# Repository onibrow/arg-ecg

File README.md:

# Arias Research Group - BLE ECG

## References

### BLE

Task - Use the nRF52 Development Kit to send ECG data from the ADAS1000 over BLE to a phone to record data.

After careful assesment, I've decided to move forward with the Arduino BLEPeripheral library, after finding that someone has ported the SoftDevice functionality to Arduino IDE. This was mainly due to my unfamiliarity with the BLE stack, and the daunting, semeingly unknown and unfriendly Nordic toolchain.

To get it to work, I had to install a few packages:

```
libstdc++5
lib32-libstdc++5
libudev0-shim
gperf
lib32-attr
lib32-libcap
lib32-libgpg-error
libg32-libgcrypt
lib32-system
lib32-libudev0-shim
```

[nRF5 board files](https://github.com/sandeepmistry/arduino-nRF5)

[Arduino BLEPeripheral](https://github.com/sandeepmistry/arduino-BLEPeripheral)



### ADAS1000

[ADAS1000 Datasheet](https://www.analog.com/media/en/technical-documentation/data-sheets/ADAS1000_1000-1_1000-2.pdf)

[Eval Board Datasheet](http://www.analog.com/media/en/technical-documentation/user-guides/UG-426.pdf)

[Reference Design](https://www.analog.com/media/en/reference-design-documentation/reference-designs/CN0308.pdf)

There are two ADAS's on the eval board, one master one slave for a total of 12 electrode input. We'll utilize only 5 of them from the master chip using the pins LA, RA, LL, RLD, V1, V2. RLD (Right Leg Driver) can also be used as the common mode electrode. We can choose different electrode setups after we get the hardware to work by toggling what we want to use and get the optimal setup

SPI communication details

* Clock Polarity: Idle HIGH
* Clock Phase: Data is clocked into ADAS during the rising edges of SCLK, and shifted out (to be read) on falling edges of SCLK

[SPI Register Defs Page 60](https://www.analog.com/media/en/technical-documentation/data-sheets/ADAS1000_1000-1_1000-2.pdf)

### CC3200MOD\[DEPRACATED\] (WiFi)

[CC3200MOD Datasheet](http://www.ti.com/lit/ds/swrs166/swrs166.pdf)

[CC3200MOD LaunchPad User Guide](http://www.ti.com/lit/ug/swru397a/swru397a.pdf)

[CC3200MOD LaunchPad Schematic](http://www.ti.com/lit/df/tidrc48/tidrc48.pdf)

[CC3200 Jumper Settings](http://energia.nu/guide/install/cc3200-guide/)

[CC3200 SPI <-> ADAS1000](https://ez.analog.com/linux-device-drivers/microcontroller-no-os-drivers/f/q-a/88100/adas-1000-to-arduino-code)

[More SPI stuff](https://www.element14.com/community/thread/46120/l/adas1000-interfacing-by-arduino-uno?displayFullThread=true)

## Other Wifi Modules

[ThingSpeak](https://thingspeak.com/)

[ESP8266](https://www.sparkfun.com/products/13678)

## IoT Server

Thinger.io is pretty nice - also has good integration with the launchpad - [Link](http://docs.thinger.io/arduino/#installation)

## Parts

All SMD components will be 0602 unless specified.

[8.192MHz](https://www.digikey.com/product-detail/en/citizen-finedevice-co-ltd/CM309S8.192MABJT/300-2039-1-ND/482155)

[1uH Inductor](https://www.digikey.com/product-detail/en/tdk-corporation/MLZ2012M1R0HT000/445-8657-1-ND/3077939)

[Chip Antenna](https://www.digikey.com/product-detail/en/taiyo-yuden/AH316M245001-T/587-2200-1-ND/2002898)

[DP3T](https://www.digikey.com/product-detail/en/c-k/JS203011JCQN/CKN10725CT-ND/6137639)

[2Pin JST](https://www.digikey.com/product-detail/en/jst-sales-america-inc/B2B-XH-A(LF)(SN)/455-2247-ND/1651045)

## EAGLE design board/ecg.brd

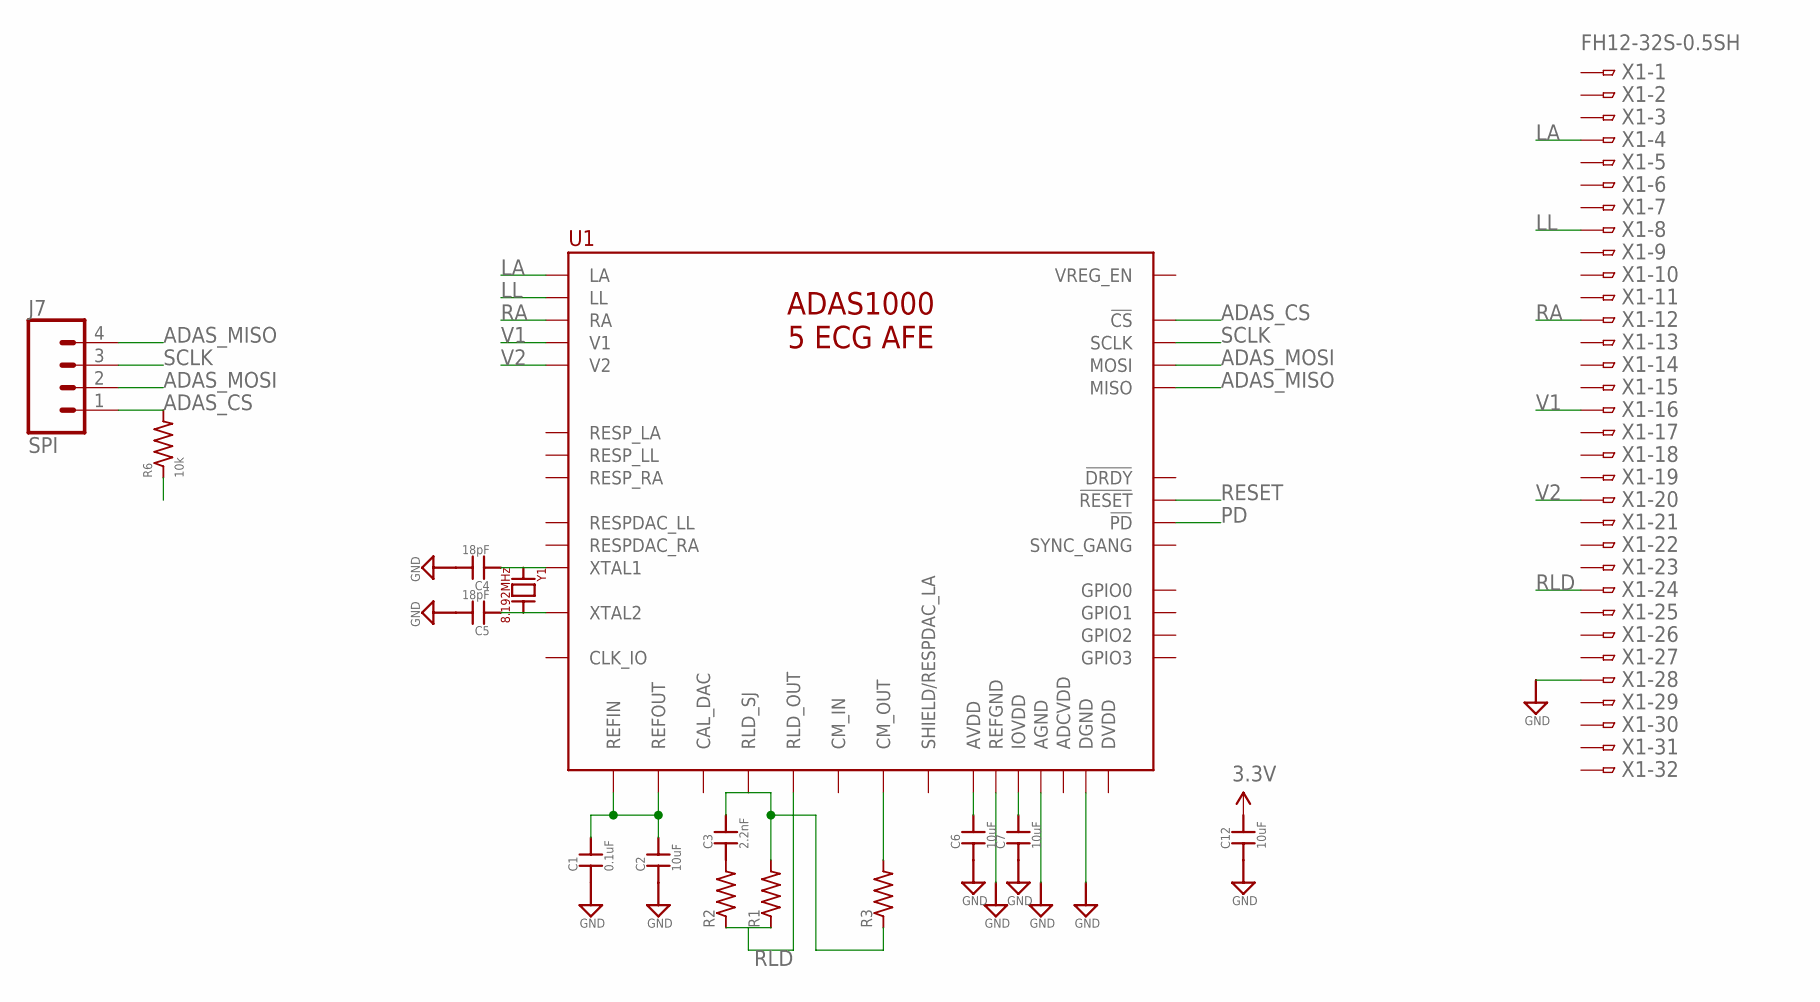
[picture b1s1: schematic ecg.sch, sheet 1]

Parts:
C1: 0.1uF; 0603-CAP
C2, C6, C7, C12: 10uF; 0603-CAP
C3: 2.2nF; 0603-CAP
C4, C5: 18pF; 0603-CAP
J7: SPI; 1X04
R1: 4M; R0603
R2: 100k; R0603
R3: 40k; R0603
R6: 10k; R0603
U1: ADAS1000; QFP50P1200X1200X160-65N
X1: FH12-32S-0.5SH
Y1: 8.192MHz; HC-49

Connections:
3.3V: C6.2, C7.2, C12.2, R6.1, U1.18 (AVDD), U1.23 (AVDD), U1.35 (IOVDD), U1.46 (IOVDD), U1.58 (AVDD), U1.63 (AVDD); also elsewhere on the board
ADAS_CS: J7.1, R6.2, U1.41 (!CS); also elsewhere on the board
ADAS_MISO: J7.4, U1.45 (MISO); also elsewhere on the board
ADAS_MOSI: J7.2, U1.43 (MOSI); also elsewhere on the board
GND: C1.1, C2.1, C4.2, C5.2, C6.1, C7.1, C12.1, U1.2 (AGND), U1.7 (REFGND), U1.15 (AGND), U1.24 (AGND), U1.25 (AGND), U1.31 (DGND), U1.34 (DGND), U1.40 (DGND), U1.47 (DGND), U1.50 (DGND), U1.56 (AGND), U1.57 (AGND), X1.28; also elsewhere on the board
LA: U1.10 (LA), X1.4
LL: U1.11 (LL), X1.8
unnamed: C1.2, C2.2, U1.8 (REFOUT), U1.9 (REFIN)
unnamed: C3.2, R1.2, R3.1, U1.21 (RLD_SJ)
unnamed: C3.1, R2.2
unnamed: R3.2, U1.22 (CM_OUT)
unnamed: C4.1, U1.27 (XTAL1), Y1.A
unnamed: C5.1, U1.28 (XTAL2), Y1.B
PD: U1.53 (!PD)
RA: U1.12 (RA), X1.12
RESET: U1.54 (!RESET)
RLD: R1.1, R2.1, U1.20 (RLD_OUT), X1.24
SCLK: J7.3, U1.44 (SCLK); also elsewhere on the board
V1: U1.13 (V1), X1.16
V2: U1.14 (V2), X1.20

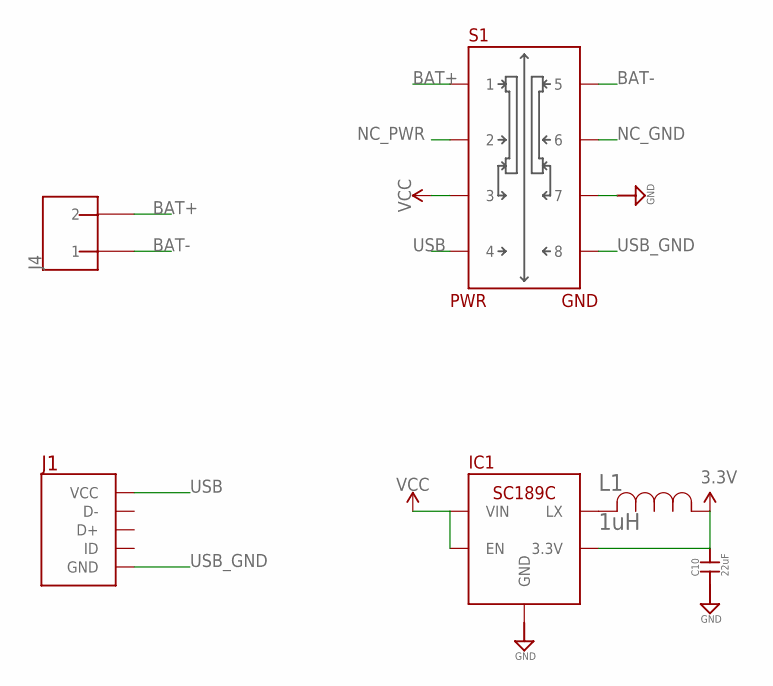
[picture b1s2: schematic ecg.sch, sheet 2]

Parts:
C10: 22uF; 0603-CAP
IC1: SC189C; SOT23-5
J1: USB_MICRO
J4: 2_PIN_JST-XH
L1: 1uH; IND_2012
S1: DP3T

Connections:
3.3V: C10.2, IC1.4 (3.3V), L1.1; also elsewhere on the board
BAT+: J4.P$2 (2), S1.1
BAT-: J4.P$1 (1), S1.5
GND: C10.1, IC1.2 (GND), S1.7; also elsewhere on the board
unnamed: IC1.5 (LX), L1.2
NC_GND: S1.6
NC_PWR: S1.2
USB: J1.VCC, S1.4
USB_GND: J1.GND, S1.8
VCC: IC1.1 (VIN), IC1.3 (EN), S1.3

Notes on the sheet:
PWR
GND

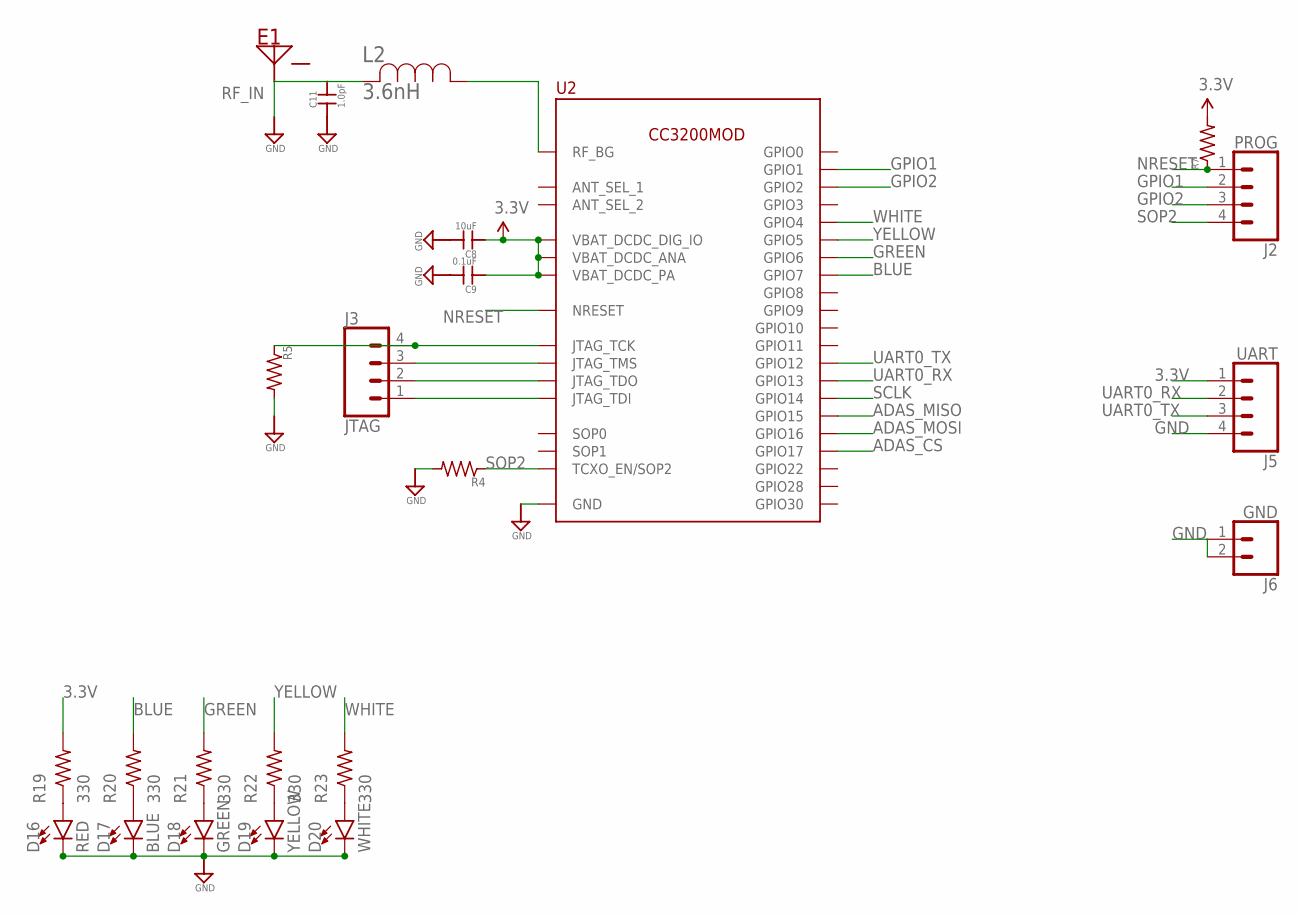
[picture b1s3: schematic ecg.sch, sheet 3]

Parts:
C8: 10uF; 0603-CAP
C9: 0.1uF; 0603-CAP
C11: 1.0pF; 0603-CAP
D16: RED; LED-0603
D17: BLUE; LED-0603
D18: GREEN; LED-0603
D19: YELLOW; LED-0603
D20: WHITE; LED-0603
E1: AH316M245001-T; CHIP_ANT
J2: PROG; 1X04
J3: JTAG; 1X04
J5: UART; 1X04
J6: GND; 1X02
L2: 3.6nH; IND0402_22N_TAI
R4: 2.7k; R0603
R5: 100k; R0603
R7: R-US_R0603; R0603
R19, R20, R21, R22, R23: 330; R0402
U2: CC3200MOD; 63-SMD

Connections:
3.3V: C8.1, C9.1, J5.1, R7.2, R19.2, U2.P$36 (VBAT_DCDC_ANA), U2.P$37 (VBAT_DCDC_PA), U2.P$40 (VBAT_DCDC_DIG_IO); also elsewhere on the board
ADAS_CS: U2.P$8 (GPIO17); also elsewhere on the board
ADAS_MISO: U2.P$6 (GPIO15); also elsewhere on the board
ADAS_MOSI: U2.P$7 (GPIO16); also elsewhere on the board
BLUE: R20.2, U2.P$52 (GPIO7)
GND: C8.2, C9.2, C11.1, D16.C, D17.C, D18.C, D19.C, D20.C, J5.4, J6.1, J6.2, R4.2, R5.2, U2.P$1 (GND), U2.P$2 (GND), U2.P$16 (GND), U2.P$27 (GND), U2.P$28 (GND), U2.P$30 (GND), U2.P$32 (GND), U2.P$38 (GND), U2.P$43 (GND), U2.P$55 (GND), U2.P$56 (GND), U2.P$57 (GND), U2.P$58 (GND), U2.P$59 (GND), U2.P$60 (GND), U2.P$61 (GND), U2.P$62 (GND), U2.P$63 (GND); also elsewhere on the board
GPIO1: J2.2, U2.P$46 (GPIO1)
GPIO2: J2.3, U2.P$47 (GPIO2)
GREEN: R21.2, U2.P$51 (GPIO6)
unnamed: J3.4, R5.1, U2.P$21 (JTAG_TCK)
unnamed: J3.3, U2.P$22 (JTAG_TMS)
unnamed: J3.2, U2.P$18 (JTAG_TDO)
unnamed: J3.1, U2.P$12 (JTAG_TDI)
unnamed: D16.A, R19.1
unnamed: D17.A, R20.1
unnamed: D18.A, R21.1
unnamed: D19.A, R22.1
unnamed: D20.A, R23.1
NRESET: J2.1, R7.1, U2.P$35 (NRESET)
RF_BG: L2.1, U2.P$31 (RF_BG)
RF_IN: C11.2, E1.INPUT, L2.2
SCLK: U2.P$5 (GPIO14); also elsewhere on the board
SOP2: J2.4, R4.1, U2.P$23 (TCXO_EN/SOP2)
UART0_RX: J5.2, U2.P$10 (GPIO13)
UART0_TX: J5.3, U2.P$9 (GPIO12)
WHITE: R23.2, U2.P$49 (GPIO4)
YELLOW: R22.2, U2.P$50 (GPIO5)

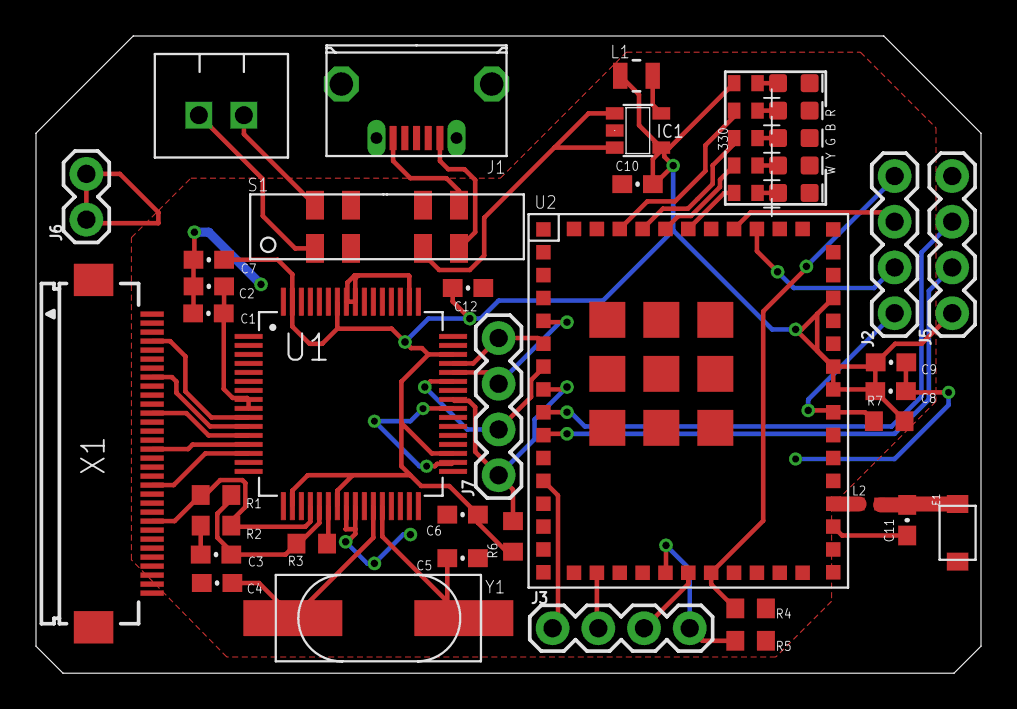
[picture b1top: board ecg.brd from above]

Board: 2 copper layers, 52.5 x 35.4 mm, 45 parts (0 on the bottom side), 45 nets.

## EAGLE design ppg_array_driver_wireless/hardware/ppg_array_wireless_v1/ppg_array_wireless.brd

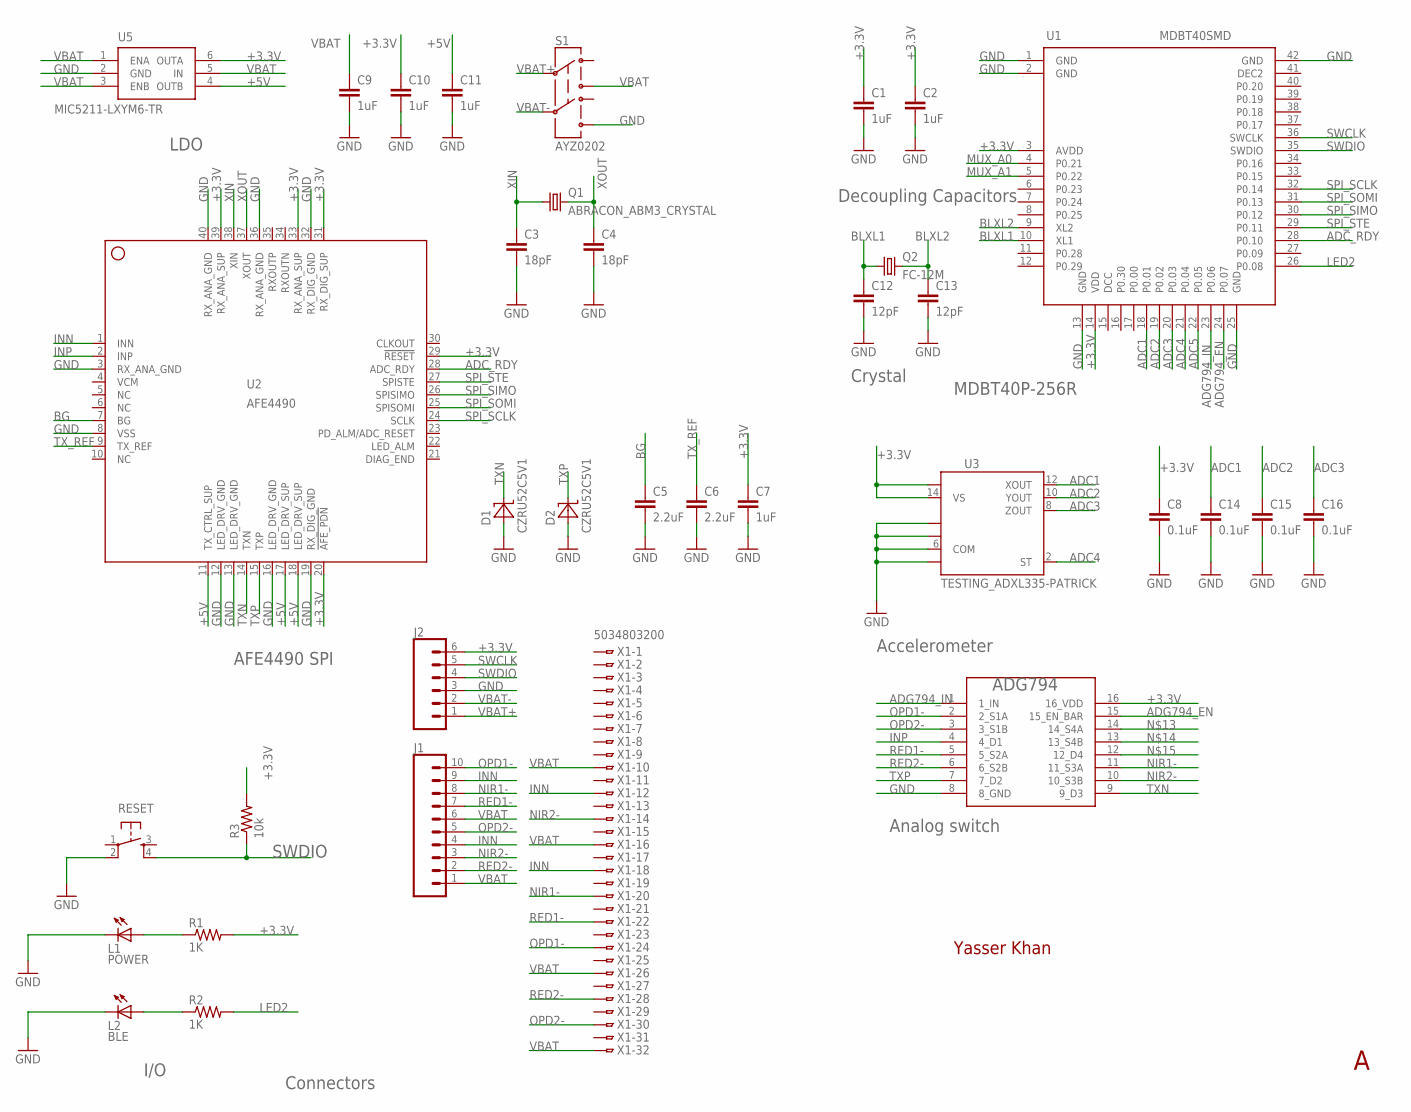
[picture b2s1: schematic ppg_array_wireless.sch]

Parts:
C1, C2, C7, C9, C10, C11: 1uF; 0603-CAP
C3, C4: 18pF; 0603-CAP
C5, C6: 2.2uF; 0603-CAP
C8, C14, C15, C16: 0.1uF; 0603-CAP
C12, C13: 12pF; 0603-CAP
D1, D2: CZRU52C5V1
J1: CONN_10"; 1X10
J2: CONN_06SILK_FEMALE_PTH; 1X06
L1: POWER; CHIP-LED0603
L2: BLE; CHIP-LED0603
Q1: ABRACON_ABM3_CRYSTAL
Q2: FC-12M
R1, R2: 1K; 0603-RES
R3: 10k; 0603-RES
RESET: TAC_SWITCHSMD; TACTILE_SWITCH_SMD
S1: AYZ0202
U1: MDBT40SMD; MDBT40
U2: AFE4490; QFN40-6X6
U3: TESTING_ADXL335-PATRICK; TESTING_LFCSP-16
U4: ADG794; QSOP16
U5: MIC5211-LXYM6-TR; SOT-23-6
X1: 5034803200

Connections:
+3.3V: C1.1, C2.1, C7.1, C8.1, C10.1, J2.6, R1.2, R3.2, U1.3 (AVDD), U1.14 (VDD), U2.20 (!AFE_PDN), U2.29 (!RESET), U2.31 (RX_DIG_SUP), U2.33 (RX_ANA_SUP), U2.39 (RX_ANA_SUP), U3.14 (VS), U3.15 (VS), U4.16 (16_VDD), U5.6 (OUTA)
+5V: C11.1, U2.11 (TX_CTRL_SUP), U2.17 (LED_DRV_SUP), U2.18 (LED_DRV_SUP), U5.4 (OUTB)
ADC1: C14.1, U1.18 (P0.01), U3.12 (XOUT)
ADC2: C15.1, U1.19 (P0.02), U3.10 (YOUT)
ADC3: C16.1, U1.20 (P0.03), U3.8 (ZOUT)
ADC4: U1.21 (P0.04), U3.2 (ST)
ADC5: U1.22 (P0.05)
ADC_RDY: U1.28 (P0.10), U2.28 (ADC_RDY)
ADG794_EN: U1.24 (P0.07), U4.15 (15_EN_BAR)
ADG794_IN: U1.23 (P0.06), U4.1 (1_IN)
BG: C5.1, U2.7 (BG)
BLXL1: C12.1, Q2.1, U1.10 (XL1)
BLXL2: C13.1, Q2.2, U1.9 (XL2)
GND: C1.2, C2.2, C3.2, C4.2, C5.2, C6.2, C7.2, C8.2, C9.2, C10.2, C11.2, C12.2, C13.2, C14.2, C15.2, C16.2, D1.A, D2.A, J2.3, L1.C, L2.C, RESET.2, S1.4 (6), U1.1 (GND), U1.2 (GND), U1.13 (GND), U1.25 (GND), U1.42 (GND), U2.3 (RX_ANA_GND), U2.8 (VSS), U2.12 (LED_DRV_GND), U2.13 (LED_DRV_GND), U2.16 (LED_DRV_GND), U2.19 (RX_DIG_GND), U2.32 (RX_DIG_GND), U2.36 (RX_ANA_GND), U2.40 (RX_ANA_GND), U2.EXP@1 (GND), U2.EXP@2 (GND), U2.EXP@3 (GND), U2.EXP@4 (GND), U2.EXP@5 (GND), U2.EXP@6 (GND), U2.EXP@7 (GND), U2.EXP@8 (GND), U2.EXP@9 (GND), U2.EXP@10 (GND), U2.EXP@11 (GND), U2.EXP@12 (GND), U2.EXP@13 (GND), U2.EXP@14 (GND), U2.EXP@15 (GND), U2.EXP@16 (GND), U2.PWR@1 (GND), U2.PWR@2 (GND), U3.3 (COM), U3.5 (COM), U3.6 (COM), U3.7 (COM), U4.8 (8_GND), U5.2 (GND)
INN: J1.4, J1.9, U2.1 (INN), X1.12, X1.18
INP: U2.2 (INP), U4.4 (4_D1)
LED2: R2.2, U1.26 (P0.08)
MUX_A0: U1.4 (P0.21)
MUX_A1: U1.5 (P0.22)
unnamed: L1.A, R1.1
unnamed: L2.A, R2.1
NIR1-: J1.8, U4.11 (11_S3A), X1.20
NIR2-: J1.3, U4.10 (10_S3B), X1.14
OPD1-: J1.10, U4.2 (2_S1A), X1.24
OPD2-: J1.5, U4.3 (3_S1B), X1.30
RED1-: J1.7, U4.5 (5_S2A), X1.22
RED2-: J1.2, U4.6 (6_S2B), X1.28
SPI_SCLK: U1.32 (P0.14), U2.24 (SCLK)
SPI_SIMO: U1.30 (P0.12), U2.26 (SPISIMO)
SPI_SOMI: U1.31 (P0.13), U2.25 (SPISOMI)
SPI_STE: U1.29 (P0.11), U2.27 (SPISTE)
SWCLK: J2.5, U1.36 (SWCLK)
SWDIO: J2.4, R3.1, RESET.4, U1.35 (SWDIO)
TXN: D1.C, U2.14 (TXN), U4.9 (9_D3)
TXP: D2.C, U2.15 (TXP), U4.7 (7_D2)
TX_REF: C6.1, U2.9 (TX_REF)
VBAT: C9.1, J1.1, J1.6, S1.1 (3), U5.1 (ENA), U5.3 (ENB), U5.5 (IN), X1.10, X1.16, X1.26, X1.32
VBAT+: J2.1, S1.2
VBAT-: J2.2, S1.5
XIN: C3.1, Q1.P$1 (1), U2.38 (XIN)
XOUT: C4.1, Q1.P$2 (2), U2.37 (XOUT)

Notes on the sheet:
LDO
AFE4490 SPI
I/O
Connectors
MDBT40P-256R
Yasser Khan
Crystal
Decoupling Capacitors
Accelerometer
Analog switch

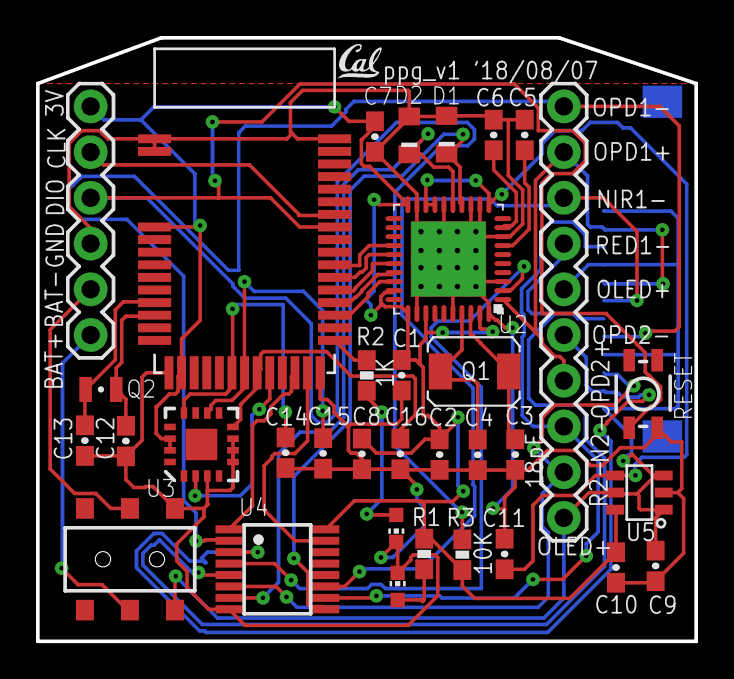
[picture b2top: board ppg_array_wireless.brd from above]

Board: 2 copper layers, 36.6 x 33.5 mm, 36 parts (1 on the bottom side), 38 nets.

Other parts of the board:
U$1: CAL

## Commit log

2018-05-23 Add gitignore
2018-05-23 add sensor test ino file
2018-05-23 do some more work
2018-05-24 update code for heartbeat on request
2018-09-09 start docomunetation
2018-09-09 small pinout blurb
2018-09-10 add trouble shooting steps
2018-09-12 add some testing info
2018-09-17 add cc3200mod chip info
2018-11-23 add some useful links
2018-11-25 start layout
2018-11-25 add eagle stuff to gitignore
2018-11-25 remove backup files
2018-11-25 do some power work
2018-11-25 add mod reference
2018-11-26 do tons of library work and nearly wrap up schematic
2018-11-29 add yassers notes
2018-12-02 Clean up readme
2018-12-02 add yassers ble
2018-12-02 make progress with the board
2018-12-02 organize images
2018-12-03 add jst
2018-12-06 ignore zips and jobs
2018-12-06 finish bom and replace 0402
2018-12-06 make sure the pinouts are same as te board
2019-01-23 fix antenna
2019-01-29 fix cs pin and add more links
2019-01-30 add spi pinout from adas1000 eval
2019-01-30 add more spi links
2019-01-30 small changes
2019-02-04 make sure pullup for !CS
2019-02-04 start spi test
2019-02-06 Add info about ADAS1000
2019-02-06 get code to work with adas1000
2019-02-07 strart thinger integration
2019-02-07 thinger io test
2019-03-31 start ble
2019-03-31 add nrf sdk
2019-03-31 make link
2019-03-31 fix some
2019-04-01 remove sdk
2019-04-01 config for arduiino
2019-04-01 add packages that i installed
2019-04-26 remove thing
2019-04-26 add firmware
2019-04-26 add print for frame

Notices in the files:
parts and their libraries:
SparkFun-Capacitors: Licensing: Creative Commons ShareAlike 4.0 International - https://creativecommons.org/licenses/by-sa/4.0
